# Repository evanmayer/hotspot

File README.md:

This repo contains code that is a part of the [TIME collaboration](https://ui.adsabs.harvard.edu/abs/2014SPIE.9153E..1WC/abstract).

Logo by Guochao (Jason) Sun.

# hotspot

Code for driving a cable-driven parallel robot for mapping beams on surfaces.

The robot moves and controls switchable thermal infrared sources to scan a 2D x-y plane, and is capable of absolute accuracy at the <3 mm level over a workspace ~0.40m x 0.40m.

## Running

Run `python main.py -h` for the docstring describing the command line interface.

### Example

```bash
python main.py ./data/input/geometry/frame.csv ./data/input/profiles/circle.csv
```

## Other Documentation

See the [HOWTO](HOWTO.md).

## Contributing

### Testing
Testing is accomplished with `pytest`. Passing tests are a prerequisite for committing code, and new code should come with new tests.

To run the test suite defined in the `tests` dir, change dir to the toplevel dir of the repo and execute 
```bash
pytest
```

### Pushing changes
If you need push permissions, message me. Otherwise, you may fork, create a new branch with your changes, and fill out a Pull Request to have the changes reviewed and merged in.

### How did you make your algorithm flowcharts?
[diagrams.net](https://diagrams.net)

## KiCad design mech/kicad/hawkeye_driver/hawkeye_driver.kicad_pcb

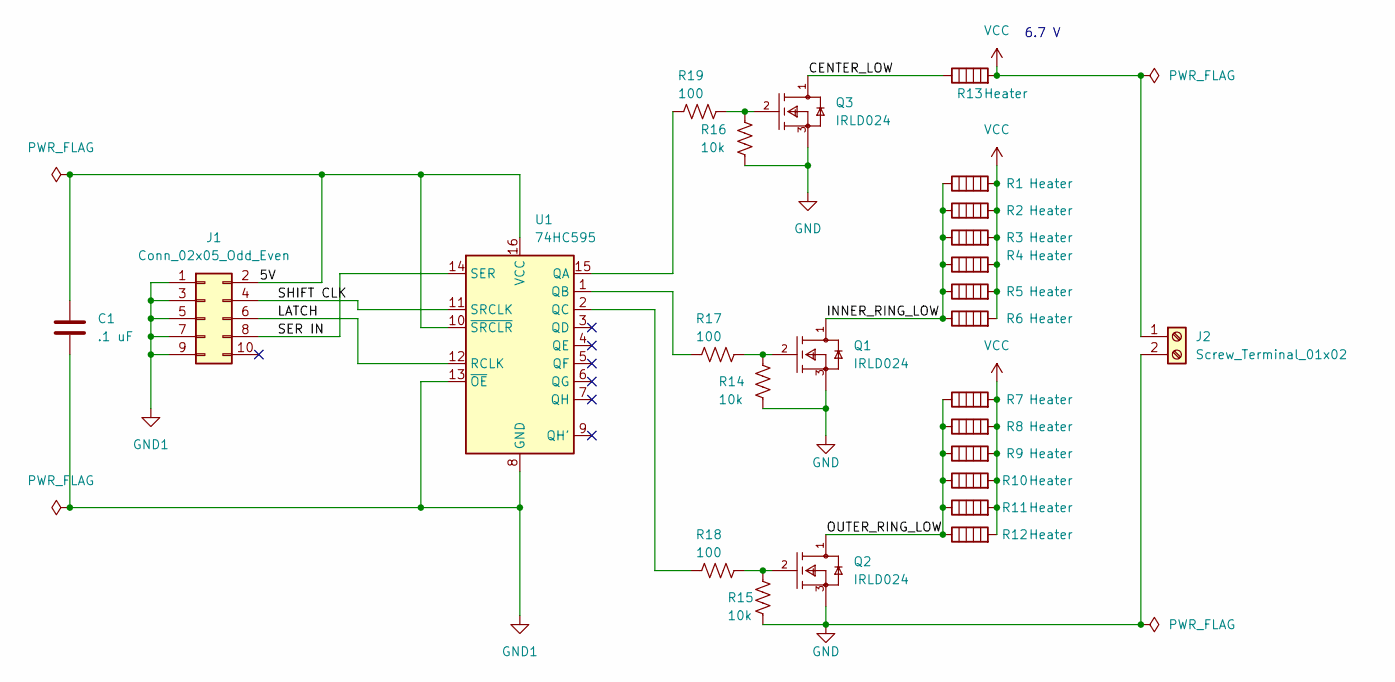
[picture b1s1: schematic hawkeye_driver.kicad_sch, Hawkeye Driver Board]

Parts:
C1: .1 uF; C_1206_3216Metric_Pad1.33x1.80mm_HandSolder
J1: Conn_02x05_Odd_Even; IDC-Header_2x05_P2.54mm_Vertical
J2: Screw_Terminal_01x02; TerminalBlock_Philmore_TB132_1x02_P5.00mm_Horizontal
Q1, Q2, Q3: IRLD024; Vishay-IRLD024-0; voltage 10V; mouser part number 844-IRLD024; digikey description MOSFET N-CH 60V 2.5A 4-DIP
R1, R2, R3, R4, R5, R6, R7, R8, R9, R10, R11, R12, R13: Heater; TO-5-3_Window
R14, R15, R16: 10k; R_1206_3216Metric_Pad1.30x1.75mm_HandSolder
R17, R18, R19: 100; R_1206_3216Metric_Pad1.30x1.75mm_HandSolder
U1: 74HC595; SO-16_3.9x9.9mm_P1.27mm

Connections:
/5V: C1.1, J1.2, U1.10 (~SRCLR), U1.16 (VCC)
/CENTER_LOW: Q3.1 (D), R13.1
/INNER_RING_LOW: Q1.1 (D), R1.1, R2.1, R3.1, R4.1, R5.1, R6.1
/LATCH: J1.6, U1.12 (RCLK)
/OUTER_RING_LOW: Q2.1 (D), R7.1, R8.1, R9.1, R10.1, R11.1, R12.1
/SER IN: J1.8, U1.14 (SER)
/SHIFT CLK: J1.4, U1.11 (SRCLK)
GND: J2.2, Q1.3 (S), Q2.3 (S), Q3.3 (S), R14.2, R15.2, R16.2
GND1: C1.2, J1.1, J1.3, J1.5, J1.7, J1.9, U1.8 (GND), U1.13 (~OE)
unnamed: Q1.2 (G), R14.1, R17.2
unnamed: Q2.2 (G), R15.1, R18.2
unnamed: Q3.2 (G), R16.1, R19.2
unnamed: R17.1, U1.1 (QB)
unnamed: R18.1, U1.2 (QC)
unnamed: R19.1, U1.15 (QA)
VCC: J2.1, R1.2, R2.2, R3.2, R4.2, R5.2, R6.2, R7.2, R8.2, R9.2, R10.2, R11.2, R12.2, R13.2

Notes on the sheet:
6.7 V

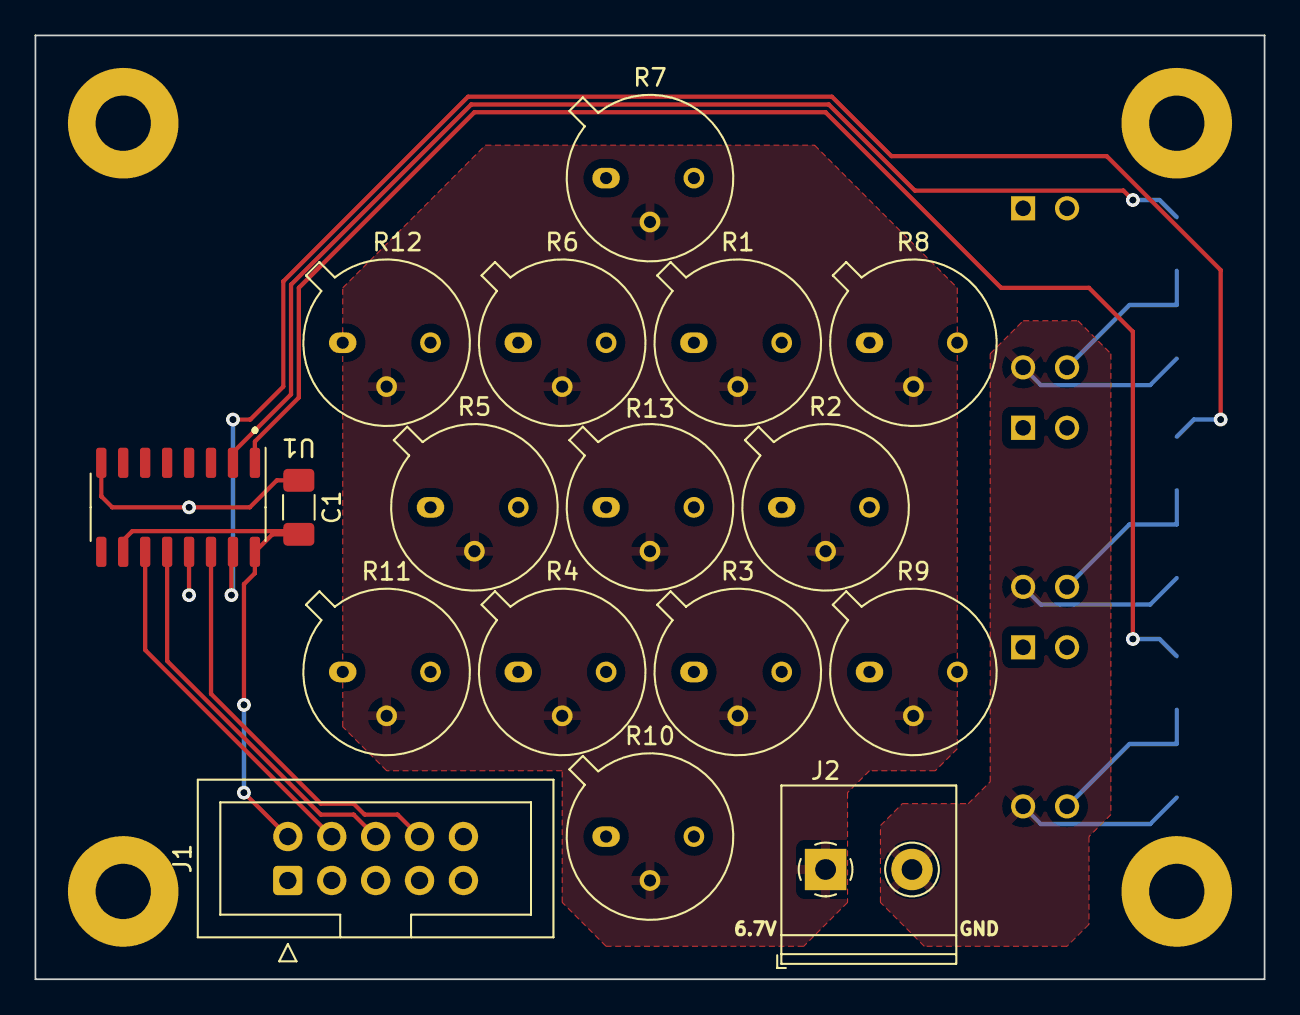
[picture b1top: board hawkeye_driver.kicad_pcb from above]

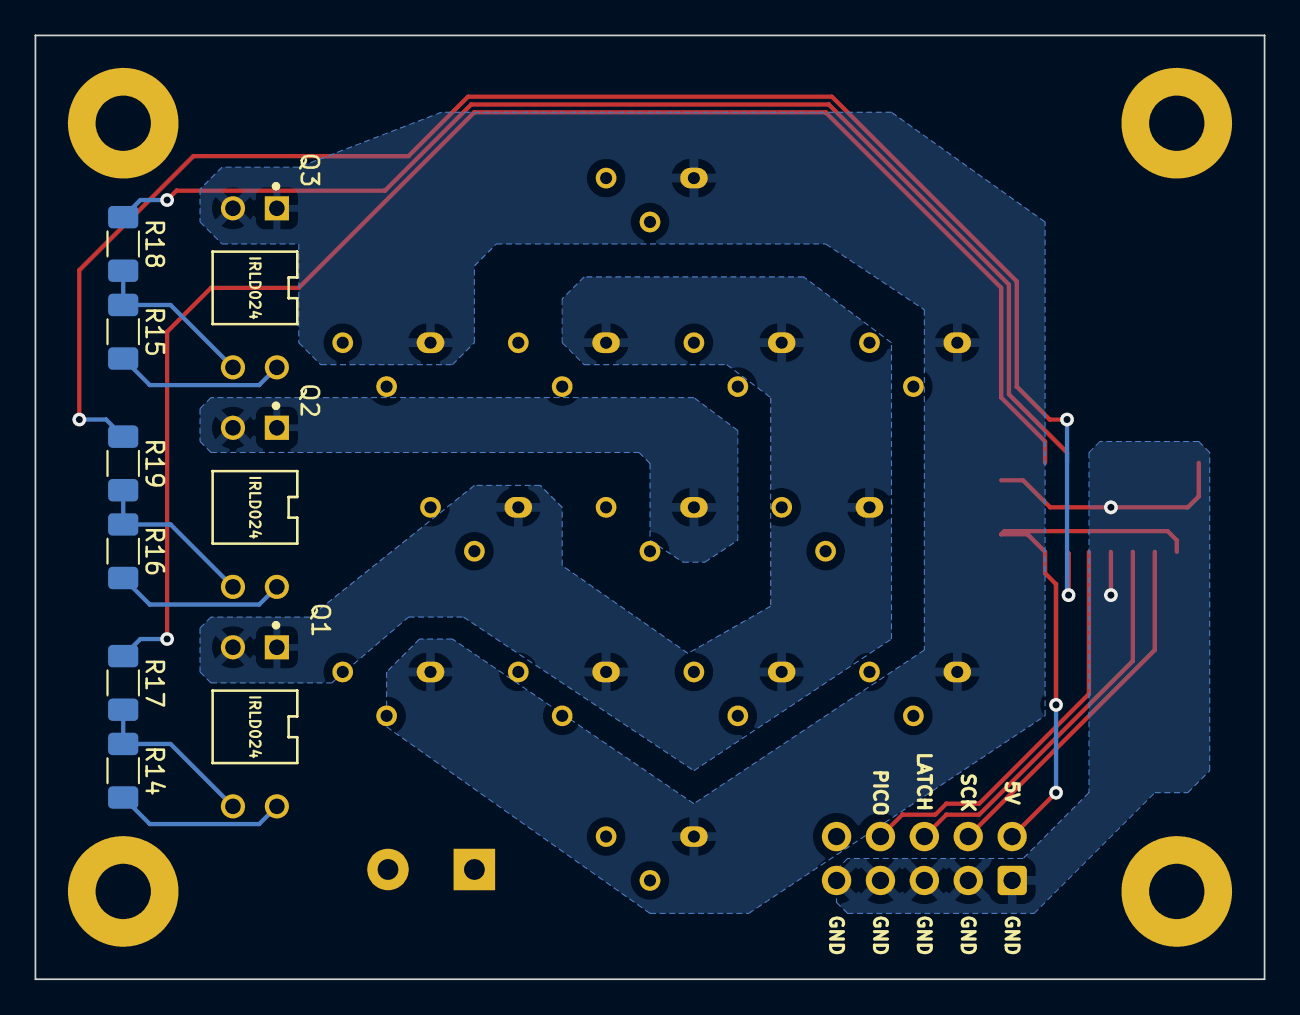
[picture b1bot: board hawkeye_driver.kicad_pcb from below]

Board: 2 copper layers, 71.1 x 54.6 mm, 26 parts (9 on the bottom side), 16 nets.

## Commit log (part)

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2021-10-27 typo
2021-10-27 algorithm flow diagram is no longer necessary after executive restructure
2021-10-27 work on docs
2021-10-27 work on executive
2021-10-27 Wrote barebones executive
2021-10-27 add second hat, remove relevant TODOs
2021-10-28 test input files
2021-10-28 updates from debugging with motors
2021-10-28 implement homing calibration and home modes.
2021-10-29 executive cleanup and docstrings, start of vis module
2021-10-30 Data logger and visualization written
2021-10-30 add 5cm radius circule profile
2021-11-01 lab benchtop setup
2021-11-01 dont forget lab bench geom file
2021-11-01 pause to update TM and plots after each move.
2021-11-01 work on doc, add imgs
2021-11-01 microstepping chng
2021-11-09 prototype single threaded motoring
2021-11-10 bresenham's line algorithm to run all steppers in a single thread
2021-11-10 add bresenahm's stepping function
2021-11-10 fix all_steppers() call
2021-11-10 remove async motor commanding and everything related to speed control
2021-11-10 stepping mode to double, updates to input files
2021-11-11 add stls for test bench setup, and version motor spool stl
2021-11-20 add cmdline parser, and enable testing in non-rpi envs
2021-11-20 forgot hw_context abstraction layer
2021-11-21 faster plot updating
2021-11-23 updates to mech stls
2021-11-23 add extra holes to motor mount
2021-11-24 update docs
2021-11-24 first cut at beam mapper config files
2021-11-24 doc updates
2021-11-27 small bugfixes
2021-11-28 mech updates, image for keepout zones, arduino stepper implementation as a backup
2021-11-28 add pyserial dep to yml
2021-11-28 pycallgraph added, test bugfix
2021-11-28 rename doc folder to docs, add pdoc html documentation, .md updates
2021-11-29 update frame geom with new measurements. home should be .15, .225.
2021-11-29 debugging updates
2021-11-30 working stepper code!
2021-12-02 work on lj integration
2021-12-03 basic lj env setup
2021-12-03 debug output and cleanup
2021-12-03 fix executive test
2021-12-04 LabJack fully integrated and benchtop tested
2021-12-04 docs and frame meas update
2021-12-06 Update rpi miniconda install instructions
2021-12-06 fix rpi env issue
2021-12-10 more integration for arduino serial backup plan
2021-12-12 debug init logging
2021-12-12 class and naming cleanup
2021-12-18 update call graph
2021-12-19 update hotspot executive flowchart
2021-12-19 serial for unix changes of no consequence
2021-12-19 rename src dir to reflect package name
2021-12-19 fix docs and tests after dir rename
2021-12-19 finished package restructure
2021-12-19 change docs solution from pdoc to portray
2021-12-19 re-gen docs with portray
2021-12-19 spacing issue
2021-12-19 rename
2021-12-19 re-gen docs, add exec flowchart to howto.md
2021-12-19 fix header
2021-12-23 make plotting cmdline optional
2021-12-23 experimental homing algorithm
2021-12-30 add auto homing prototype
2022-01-02 docs update
2022-01-02 debug and switch to auto homing
2022-01-03 work on final debugging and homing
2022-01-04 input file changes
2022-01-04 debugging/hacking
2022-01-04 more debugging, verified hawkeye sources work at least
2022-01-05 Debugging: additional testing for algorithm
2022-01-05 Remove hacks from executive, not actually necessary
2022-01-06 Attempt to characterize and compensate for rounding error in steps
2022-01-06 Unused code cleanup
2022-01-06 Doc updates and multiline profile bugfix
2022-01-06 fix unresonsive plots after sequence complete
2022-01-07 Create profiles for TIME optics
2022-01-07 remove unused profiles
2022-01-07 rename profiles to reflect what's inside
2022-01-07 fixed incorrect measurements of x-offsets
2022-01-07 this version actually kind of works!
2022-01-08 small change to step correction
2022-01-10 add targets for photogrammetry and script for finding them in image coords
2022-01-10 working version of measurement tool
2022-01-11 work on photogrammetry
2022-01-11 intermediate work on position finder
2022-01-12 add photos of mapper, work on photogrammetry routine
2022-01-12 more work on data analysis
2022-01-12 faster fitting, and plotting work
2022-01-12 coarse raster scans
2022-01-12 update scan pattern of coarse files for photogrammetry
2022-01-12 processed a raster scan, script updates
2022-01-13 work on raster scan error mapping
2022-01-13 redo point-to-point position mapping
2022-01-13 point-to-point script update
2022-01-13 correlate update
2022-01-14 dot pattern fitting implemented, commit before breaking current analysis routine
2022-01-14 intermediate commit of grid fitting code...kinda sorta works
2022-01-14 add images from data processing
2022-01-14 commit rotation correction code, even though it didn't help => there are tilts present
2022-01-14 results without doing rotation correction
2022-01-14 update output images
2022-01-14 new profiles for photo-g starting NW instead of SE
2022-01-14 try out a backstep aftereach move to attempt re-tensioning - bugfix
2022-01-14 revert backstepping hack
2022-01-14 upload photos and results, add a new scan for comore complete coverage of 24 in breadboard surface
2022-01-14 stop downsampling truth image for xcorr position finding
2022-01-14 commit before trying to implement projection corrections
2022-01-15 change gitignore to exclude all image files
2022-01-15 0.001 inch adjust to K2
2022-01-16 add larger footprint coarse scans
2022-01-16 more dense pattern
2022-01-16 add 9x9 profile
2022-01-16 create profiles with an additional flasher address for 5V output to MCE clock card
2022-01-17 make K1 profiles use only 1 hawkeye
2022-01-17 add 7 hawkeye K1 scan
2022-01-18 docs updated
2022-01-18 add docs html redirect
2022-01-18 update docs html
2022-01-18 Change time of Labjack TM packet to start of blink phase
2022-01-18 fix syntax highlighting
2022-01-19 html update
2022-01-19 trying to fix table of contents
2022-01-19 point from readme to howto
2022-01-19 trying to track down error sources
2022-01-21 fix TM plotting/label bug
2022-01-21 First cut implementation of adjustments for spools that change diameter
2022-01-21 fix freq in main repo
2022-01-21 measure m added to spools per rad of line
2022-01-21 dirty hack: force all steppers to skip to try to maintain equal tension
2022-01-21 undo step skipping hack, do step slackening hack
2022-01-21 fix 24in input file
2022-01-24 add cable spool charatcerization
2022-01-26 second try at characterizing angle vs. distance
2022-01-26 fix microstepping setting
2022-01-27 update geometry for aymmetrical motor mounts and fix x-coord bug
2022-01-27 bugfix 24in input file
2022-01-28 try to debug length bugs with a standalone script
2022-01-28 bugfix the bigfix
2022-01-28 experimentally determining k and r
2022-01-28 update geo create script to reflect actual measured frame geo
2022-01-29 run update on geo files
2022-01-29 adjust starting spool angles
2022-01-29 bugfixing bs
2022-01-30 manual blink mode
2022-01-31 write TM, even if the only command is a manual blink
2022-01-31 update create_geometry
2022-02-28 implement new motor angle calc for helical drum, update tests
2022-02-28 remove print statement in tests
2022-03-02 add direct call more for steppers test: wiggle in turn to ID motors
2022-03-03 new photog try
2022-03-04 workon opencv stuff
2022-03-04 update photogrammetry nb
2022-03-04 update photogrammetry
2022-03-06 photogrammetry working to better than 1mm!
2022-03-06 cautionary tales
2022-03-06 quantify photogrammetry measurement error
2022-03-07 more metrics
2022-03-08 some QoL things and constants changes for in-lab photog setup
2022-03-08 start optimizing
2022-03-08 optimizations for speed and data cleaning
2022-03-09 remove ipynb
2022-03-10 work on pg library, add back ipynb with lib calls now
2022-03-10 work on pg workflow
2022-03-15 more work on vis
2022-03-17 work on photo-g
2022-05-17 hawkeye driver kicad
2022-05-18 start working on charuco camera calibration
2022-05-18 work on charuco photogrammetry - added camera calibration
2022-05-19 work on ground planes
2022-05-19 finish ground plane rework
2022-05-20 final commit before fab
2022-05-27 init commit of ezstepper commanding code
2022-05-27 init commit of homing algorithm
2022-05-27 intermediate commit, debugging ezstepper comms
2022-05-28 tested working with one motor. pay attention that encoder changes direction with motor moves!
2022-05-30 fix typo
2022-06-02 middle of homing debugging commit
2022-06-05 update mosfet silkscreen and soldermask for errors
2022-06-05 update docs with new call graph
2022-06-07 mid-debugging cleanup
2022-06-07 fudge factor in gometry filegit add data/input/geometry/24in_breadboard.csv !
2022-06-08 good from far homing performance
2022-06-08 change arduino shift register driver to use SPI library
2022-06-10 add option to specify new profile without rehoming
2022-06-10 docs and test update
2022-06-15 update geometry files with new raft eyelet dimensions
2022-06-17 possible targetless raft tracking
2022-07-01 updates to hawkeye driver firmware
2022-07-01 add serial listening capability to hawkeye driver
2022-07-01 switch from labjack hawkeye driver to microcontroller driver
2022-07-01 update generated docs
2022-07-01 update docs text to remove labjack mentions. images forthcoming
2022-07-01 update profile generator ipynb, fix docs typos.
2022-07-12 general code cleanup
2022-07-18 update geometry after modifying motor mounts to accommodate encoder stickout
2022-07-19 update hw function docstrings, fix a visualization bug
2022-08-03 Lasts doc updates, geometry updates, profile update
2022-08-03 Update yml
2022-08-03 profile updates
2022-08-03 Add temp code for photogrammetry picturetaking
2022-08-04 update photogrammetry concurrency and yml
2022-08-08 Major updates and cleanup to profiles dir
2022-08-08 Fix pickle error in camera calibration
2022-08-08 Update profiles and post-processing
2022-09-06 work on beam sim
2022-10-24 First cut of code that calculates fresnel integral
2022-11-11 Work on fresnel code
2022-11-12 Updates before running on big pc
2022-11-12 add test: raft obscuration
2022-11-12 changes to file names
2022-11-12 Collected changes from running on office computer
2022-11-12 Clean up nb commit
2022-11-14 start adding optional gpu calcs
2022-11-14 Independent control of source image zoom and upsampling
2022-11-14 plotting changes, cropping/zooming fixes
2022-11-16 performance improvements
2022-11-16 changes to npz saving
2022-11-18 remove cell outputs
2022-11-18 Things are working on fresnel calc
2022-11-21 cudafy fresnel_zemax
2022-11-22 Testing arbitrary orientations for correctness
2022-11-22 Potential kernel bugfix
2022-11-22 animation improvements
2023-03-12 some verification folder cleanup
2023-05-11 Minor updates from using code
2023-05-13 target tracking and measurement overhaul, first cut
2023-05-13 latest as-printed calib board/target dims
2023-05-13 raft id var
2023-05-26 Performance fixes and bug improvements
2023-06-09 Bring STLs up to date with reality
2023-06-14 Changes to make spool angles better appoximate true path for all moves
2023-06-14 Make serial comms more robust at higher baudrates
2023-06-17 Updates for performance and measurement improvements
2023-06-19 Updates for more robust calibration with a finer charuco board
2023-06-20 Updates for real measurements, addition of more plots and data processing
2023-06-21 code updates for reliability
2023-06-22 Some code cleanup, new motion parameters
2023-06-23 Updates to motion parameters for performance
2023-06-24 Updates for more robust charuco board pose estimation
2023-06-24 Changes to robustify board and marker pose estimation, prettify plots
2023-06-29 Cosmetic changes to photogrammetry
2023-07-28 Add a small ipynb for paper
2023-07-28 Minor QOL updates
2023-08-11 Update measurements to be relative to origin mean. Clean up plotting
2023-10-11 Test cleanup
2023-10-12 Update conda yml
2023-10-12 Speed up environment solve, conda-forge not needed
2023-10-12 try without mamba
2023-11-15 Updates for paper plots
2023-11-15 Update and regenerate docs
2024-01-11 Add BOM for Hawkeye driver board
2024-01-11 Add pictures to BOM
2024-01-11 alt ir50 source
2024-01-11 Commit images
2024-12-16 Profile cleanup: delete those I don't anticipate to use for TIME 2024/2025
2024-12-16 more adjustability for hawkeye flashes
